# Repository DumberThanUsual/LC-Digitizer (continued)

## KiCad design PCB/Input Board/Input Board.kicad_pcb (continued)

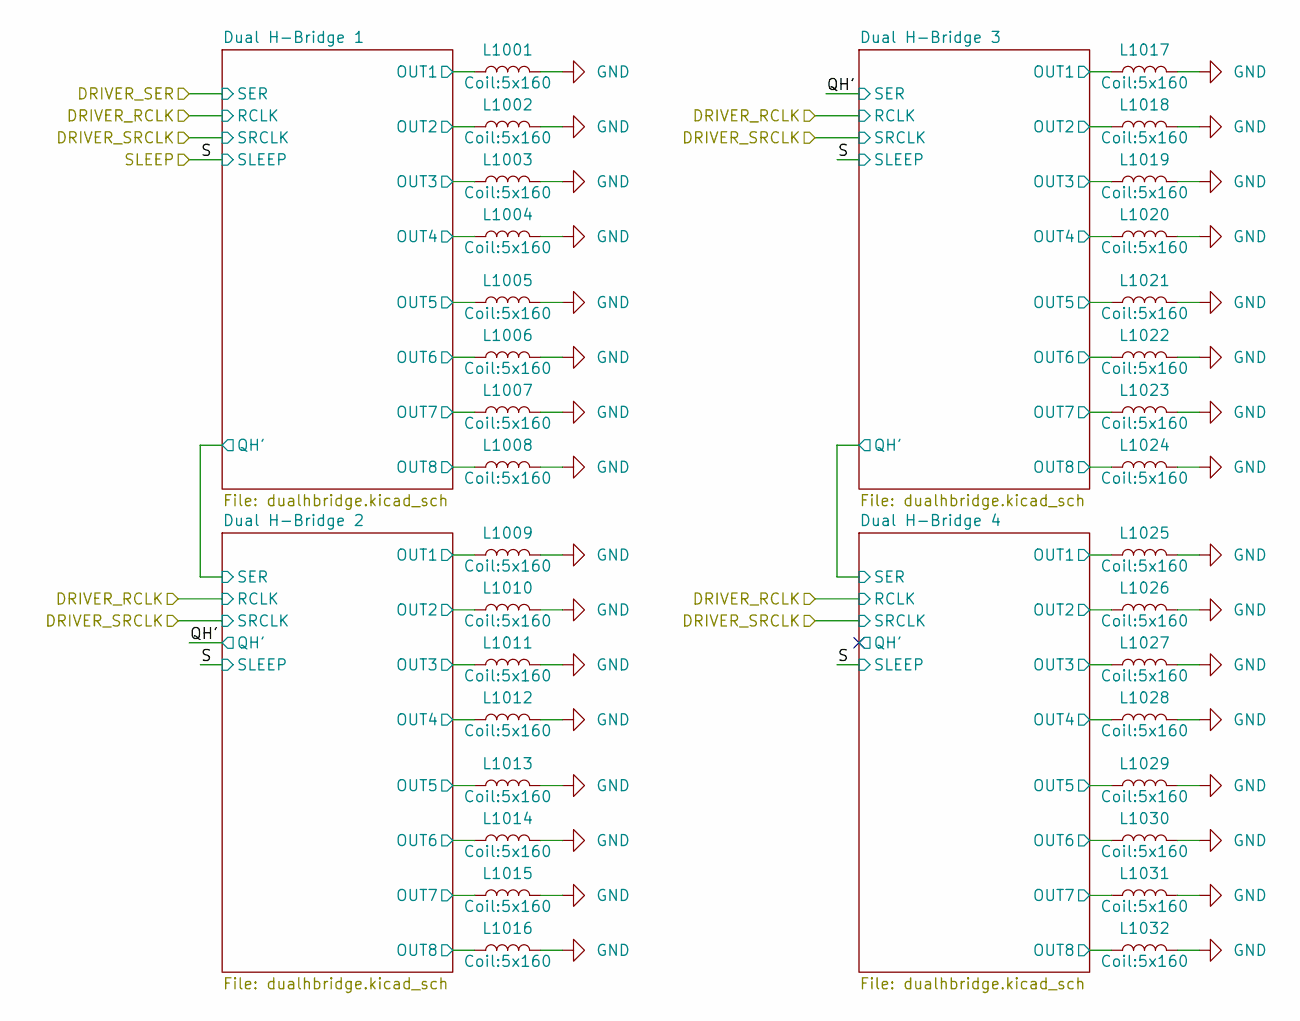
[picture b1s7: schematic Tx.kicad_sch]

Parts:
L1001, L1002, L1003, L1004, L1005, L1006, L1007, L1008, L1009, L1010, L1011, L1012, L1013, L1014, L1015, L1016, L1017, L1018, L1019, L1020, L1021, L1022, L1023, L1024, L1025, L1026, L1027, L1028, L1029, L1030, L1031, L1032: L; 5x160

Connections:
/Transmit Coils/Dual H-Bridge 1/OUT1: L1001.1; also elsewhere on the board
/Transmit Coils/Dual H-Bridge 1/OUT2: L1002.1; also elsewhere on the board
/Transmit Coils/Dual H-Bridge 1/OUT3: L1003.1; also elsewhere on the board
/Transmit Coils/Dual H-Bridge 1/OUT4: L1004.1; also elsewhere on the board
/Transmit Coils/Dual H-Bridge 1/OUT5: L1005.1; also elsewhere on the board
/Transmit Coils/Dual H-Bridge 1/OUT6: L1006.1; also elsewhere on the board
/Transmit Coils/Dual H-Bridge 1/OUT7: L1007.1; also elsewhere on the board
/Transmit Coils/Dual H-Bridge 1/OUT8: L1008.1; also elsewhere on the board
/Transmit Coils/Dual H-Bridge 2/OUT1: L1009.1; also elsewhere on the board
/Transmit Coils/Dual H-Bridge 2/OUT2: L1010.1; also elsewhere on the board
/Transmit Coils/Dual H-Bridge 2/OUT3: L1011.1; also elsewhere on the board
/Transmit Coils/Dual H-Bridge 2/OUT4: L1012.1; also elsewhere on the board
/Transmit Coils/Dual H-Bridge 2/OUT5: L1013.1; also elsewhere on the board
/Transmit Coils/Dual H-Bridge 2/OUT6: L1014.1; also elsewhere on the board
/Transmit Coils/Dual H-Bridge 2/OUT7: L1015.1; also elsewhere on the board
/Transmit Coils/Dual H-Bridge 2/OUT8: L1016.1; also elsewhere on the board
/Transmit Coils/Dual H-Bridge 3/OUT1: L1017.1; also elsewhere on the board
/Transmit Coils/Dual H-Bridge 3/OUT2: L1018.1; also elsewhere on the board
/Transmit Coils/Dual H-Bridge 3/OUT3: L1019.1; also elsewhere on the board
/Transmit Coils/Dual H-Bridge 3/OUT4: L1020.1; also elsewhere on the board
/Transmit Coils/Dual H-Bridge 3/OUT5: L1021.1; also elsewhere on the board
/Transmit Coils/Dual H-Bridge 3/OUT6: L1022.1; also elsewhere on the board
/Transmit Coils/Dual H-Bridge 3/OUT7: L1023.1; also elsewhere on the board
/Transmit Coils/Dual H-Bridge 3/OUT8: L1024.1; also elsewhere on the board
/Transmit Coils/Dual H-Bridge 4/OUT1: L1025.1; also elsewhere on the board
/Transmit Coils/Dual H-Bridge 4/OUT2: L1026.1; also elsewhere on the board
/Transmit Coils/Dual H-Bridge 4/OUT3: L1027.1; also elsewhere on the board
/Transmit Coils/Dual H-Bridge 4/OUT4: L1028.1; also elsewhere on the board
/Transmit Coils/Dual H-Bridge 4/OUT5: L1029.1; also elsewhere on the board
/Transmit Coils/Dual H-Bridge 4/OUT6: L1030.1; also elsewhere on the board
/Transmit Coils/Dual H-Bridge 4/OUT7: L1031.1; also elsewhere on the board
/Transmit Coils/Dual H-Bridge 4/OUT8: L1032.1; also elsewhere on the board
GND: L1001.2, L1002.2, L1003.2, L1004.2, L1005.2, L1006.2, L1007.2, L1008.2, L1009.2, L1010.2, L1011.2, L1012.2, L1013.2, L1014.2, L1015.2, L1016.2, L1017.2, L1018.2, L1019.2, L1020.2, L1021.2, L1022.2, L1023.2, L1024.2, L1025.2, L1026.2, L1027.2, L1028.2, L1029.2, L1030.2, L1031.2, L1032.2; also elsewhere on the board

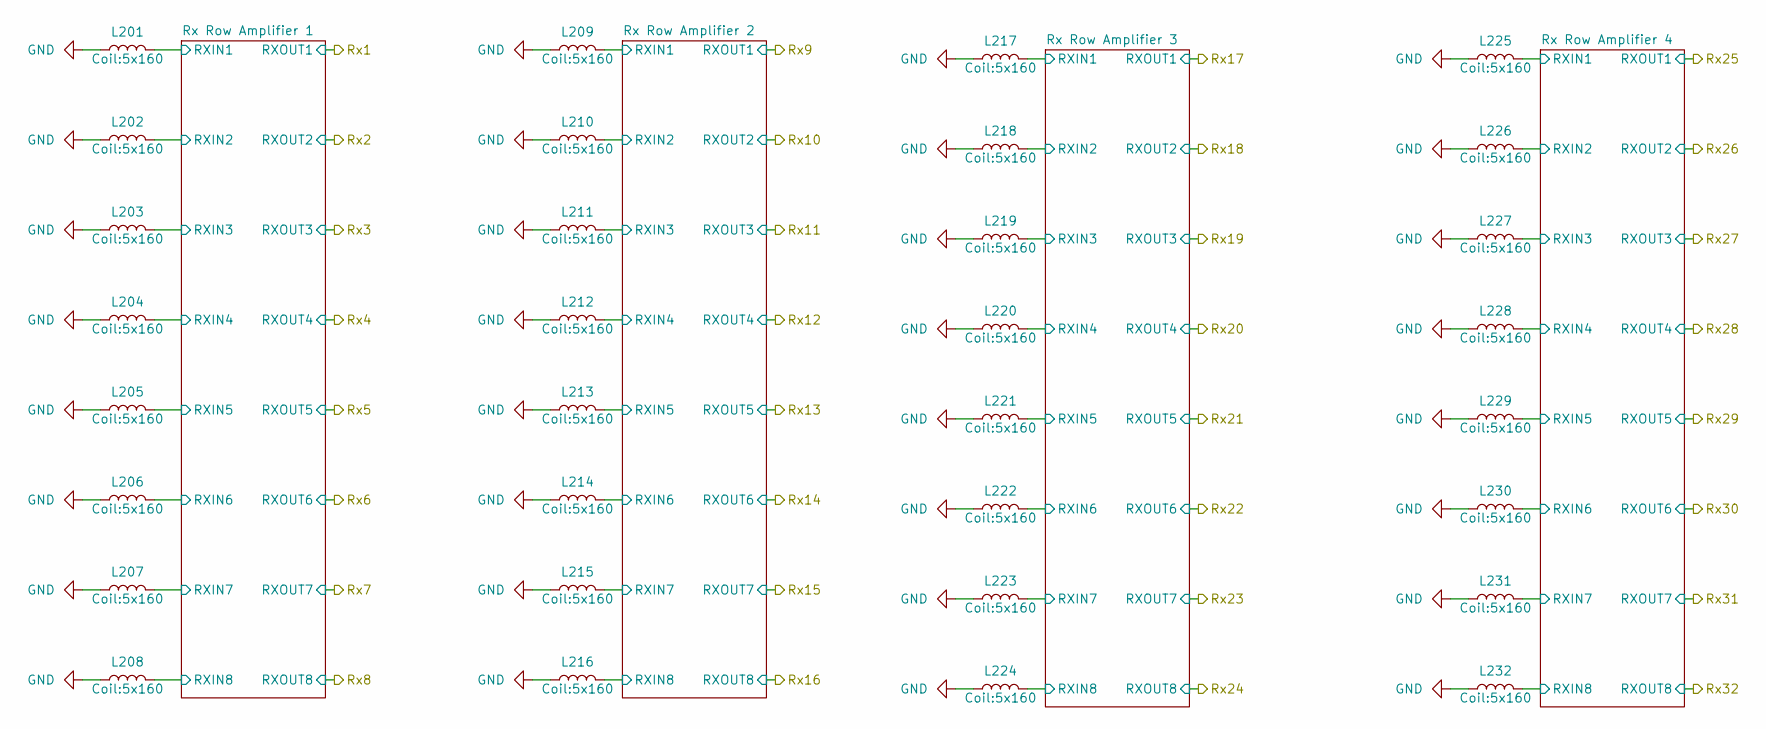
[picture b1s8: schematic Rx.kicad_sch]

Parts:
L201, L202, L203, L204, L205, L206, L207, L208, L209, L210, L211, L212, L213, L214, L215, L216, L217, L218, L219, L220, L221, L222, L223, L224, L225, L226, L227, L228, L229, L230, L231, L232: L; 5x160

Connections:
/Receiver Stage/Rx Row Amplifier 1/RXIN1: L201.2; also elsewhere on the board
/Receiver Stage/Rx Row Amplifier 1/RXIN2: L202.2; also elsewhere on the board
/Receiver Stage/Rx Row Amplifier 1/RXIN3: L203.2; also elsewhere on the board
/Receiver Stage/Rx Row Amplifier 1/RXIN4: L204.2; also elsewhere on the board
/Receiver Stage/Rx Row Amplifier 1/RXIN5: L205.2; also elsewhere on the board
/Receiver Stage/Rx Row Amplifier 1/RXIN6: L206.2; also elsewhere on the board
/Receiver Stage/Rx Row Amplifier 1/RXIN7: L207.2; also elsewhere on the board
/Receiver Stage/Rx Row Amplifier 1/RXIN8: L208.2; also elsewhere on the board
/Receiver Stage/Rx Row Amplifier 2/RXIN1: L209.2; also elsewhere on the board
/Receiver Stage/Rx Row Amplifier 2/RXIN2: L210.2; also elsewhere on the board
/Receiver Stage/Rx Row Amplifier 2/RXIN3: L211.2; also elsewhere on the board
/Receiver Stage/Rx Row Amplifier 2/RXIN4: L212.2; also elsewhere on the board
/Receiver Stage/Rx Row Amplifier 2/RXIN5: L213.2; also elsewhere on the board
/Receiver Stage/Rx Row Amplifier 2/RXIN6: L214.2; also elsewhere on the board
/Receiver Stage/Rx Row Amplifier 2/RXIN7: L215.2; also elsewhere on the board
/Receiver Stage/Rx Row Amplifier 2/RXIN8: L216.2; also elsewhere on the board
/Receiver Stage/Rx Row Amplifier 3/RXIN1: L217.2; also elsewhere on the board
/Receiver Stage/Rx Row Amplifier 3/RXIN2: L218.2; also elsewhere on the board
/Receiver Stage/Rx Row Amplifier 3/RXIN3: L219.2; also elsewhere on the board
/Receiver Stage/Rx Row Amplifier 3/RXIN4: L220.2; also elsewhere on the board
/Receiver Stage/Rx Row Amplifier 3/RXIN5: L221.2; also elsewhere on the board
/Receiver Stage/Rx Row Amplifier 3/RXIN6: L222.2; also elsewhere on the board
/Receiver Stage/Rx Row Amplifier 3/RXIN7: L223.2; also elsewhere on the board
/Receiver Stage/Rx Row Amplifier 3/RXIN8: L224.2; also elsewhere on the board
/Receiver Stage/Rx Row Amplifier 4/RXIN1: L225.2; also elsewhere on the board
/Receiver Stage/Rx Row Amplifier 4/RXIN2: L226.2; also elsewhere on the board
/Receiver Stage/Rx Row Amplifier 4/RXIN3: L227.2; also elsewhere on the board
/Receiver Stage/Rx Row Amplifier 4/RXIN4: L228.2; also elsewhere on the board
/Receiver Stage/Rx Row Amplifier 4/RXIN5: L229.2; also elsewhere on the board
/Receiver Stage/Rx Row Amplifier 4/RXIN6: L230.2; also elsewhere on the board
/Receiver Stage/Rx Row Amplifier 4/RXIN7: L231.2; also elsewhere on the board
/Receiver Stage/Rx Row Amplifier 4/RXIN8: L232.2; also elsewhere on the board
GND: L201.1, L202.1, L203.1, L204.1, L205.1, L206.1, L207.1, L208.1, L209.1, L210.1, L211.1, L212.1, L213.1, L214.1, L215.1, L216.1, L217.1, L218.1, L219.1, L220.1, L221.1, L222.1, L223.1, L224.1, L225.1, L226.1, L227.1, L228.1, L229.1, L230.1, L231.1, L232.1; also elsewhere on the board

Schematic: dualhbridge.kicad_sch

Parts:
C1101, C1102, C1103, C1104, C1105: 100n; C_0603_1608Metric
U1101: 74HCS95; DHVQFN-16-1EP_2.5x3.5mm_P0.5mm_EP1x2mm
U1102, U1103, U1104, U1105: DRV8837; WSON-8-1EP_2x2mm_P0.5mm_EP0.9x1.6mm

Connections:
+5V: C1101.2, C1102.2, C1103.2, C1104.2, C1105.2, U1101.10 (~SRCLR), U1101.16 (VCC), U1102.1 (VM), U1102.8 (VCC), U1103.1 (VM), U1103.8 (VCC), U1104.1 (VM), U1104.8 (VCC), U1105.1 (VM), U1105.8 (VCC); also elsewhere on the board
/Measurement & Control/TX_RCLK: U1101.12 (RCLK); also elsewhere on the board
/Measurement & Control/TX_SDO: U1101.14 (SER); also elsewhere on the board
/Measurement & Control/TX_SLEEP: U1102.7 (~SLEEP), U1103.7 (~SLEEP), U1104.7 (~SLEEP), U1105.7 (~SLEEP); also elsewhere on the board
/Measurement & Control/TX_SRCLK: U1101.11 (SRCLK); also elsewhere on the board
/Transmit Coils/Dual H-Bridge 1/OUT1: U1102.2 (OUT1); also elsewhere on the board
/Transmit Coils/Dual H-Bridge 1/OUT2: U1102.3 (OUT2); also elsewhere on the board
/Transmit Coils/Dual H-Bridge 1/OUT3: U1103.2 (OUT1); also elsewhere on the board
/Transmit Coils/Dual H-Bridge 1/OUT4: U1103.3 (OUT2); also elsewhere on the board
/Transmit Coils/Dual H-Bridge 1/OUT5: U1104.2 (OUT1); also elsewhere on the board
/Transmit Coils/Dual H-Bridge 1/OUT6: U1104.3 (OUT2); also elsewhere on the board
/Transmit Coils/Dual H-Bridge 1/OUT7: U1105.2 (OUT1); also elsewhere on the board
/Transmit Coils/Dual H-Bridge 1/OUT8: U1105.3 (OUT2); also elsewhere on the board
/Transmit Coils/Dual H-Bridge 1/QH': U1101.9 (QH'); also elsewhere on the board
GND: C1101.1, C1102.1, C1103.1, C1104.1, C1105.1, U1101.8 (GND), U1101.13 (~OE), U1101.17, U1102.4 (GND), U1102.9 (GND), U1103.4 (GND), U1103.9 (GND), U1104.4 (GND), U1104.9 (GND), U1105.4 (GND), U1105.9 (GND); also elsewhere on the board
unnamed: U1101.15 (QA), U1102.6 (IN1)
unnamed: U1101.1 (QB), U1102.5 (IN2)
unnamed: U1101.2 (QC), U1103.6 (IN1)
unnamed: U1101.3 (QD), U1103.5 (IN2)
unnamed: U1101.4 (QE), U1104.6 (IN1)
unnamed: U1101.5 (QF), U1104.5 (IN2)
unnamed: U1101.6 (QG), U1105.6 (IN1)
unnamed: U1101.7 (QH), U1105.5 (IN2)

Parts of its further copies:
C1201, C1202, C1203, C1204, C1205, C1301, C1302, C1303, C1304, C1305, C1401, C1402, C1403, C1404, C1405: 100n; C_0603_1608Metric
U1201, U1301, U1401: 74HCS95; DHVQFN-16-1EP_2.5x3.5mm_P0.5mm_EP1x2mm
U1202, U1203, U1204, U1205, U1302, U1303, U1304, U1305, U1402, U1403, U1404, U1405: DRV8837; WSON-8-1EP_2x2mm_P0.5mm_EP0.9x1.6mm

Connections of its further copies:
+5V: C1201.2, C1202.2, C1203.2, C1204.2, C1205.2, C1301.2, C1302.2, C1303.2, C1304.2, C1305.2, C1401.2, C1402.2, C1403.2, C1404.2, C1405.2, U1201.10 (~SRCLR), U1201.16 (VCC), U1202.1 (VM), U1202.8 (VCC), U1203.1 (VM), U1203.8 (VCC), U1204.1 (VM), U1204.8 (VCC), U1205.1 (VM), U1205.8 (VCC), U1301.10 (~SRCLR), U1301.16 (VCC), U1302.1 (VM), U1302.8 (VCC), U1303.1 (VM), U1303.8 (VCC), U1304.1 (VM), U1304.8 (VCC), U1305.1 (VM), U1305.8 (VCC), U1401.10 (~SRCLR), U1401.16 (VCC), U1402.1 (VM), U1402.8 (VCC), U1403.1 (VM), U1403.8 (VCC), U1404.1 (VM), U1404.8 (VCC), U1405.1 (VM), U1405.8 (VCC); also elsewhere on the board
/Measurement & Control/TX_RCLK: U1201.12 (RCLK), U1301.12 (RCLK), U1401.12 (RCLK); also elsewhere on the board
/Measurement & Control/TX_SLEEP: U1202.7 (~SLEEP), U1203.7 (~SLEEP), U1204.7 (~SLEEP), U1205.7 (~SLEEP), U1302.7 (~SLEEP), U1303.7 (~SLEEP), U1304.7 (~SLEEP), U1305.7 (~SLEEP), U1402.7 (~SLEEP), U1403.7 (~SLEEP), U1404.7 (~SLEEP), U1405.7 (~SLEEP); also elsewhere on the board
/Measurement & Control/TX_SRCLK: U1201.11 (SRCLK), U1301.11 (SRCLK), U1401.11 (SRCLK); also elsewhere on the board
/Transmit Coils/Dual H-Bridge 1/QH': U1201.14 (SER); also elsewhere on the board
/Transmit Coils/Dual H-Bridge 2/OUT1: U1202.2 (OUT1); also elsewhere on the board
/Transmit Coils/Dual H-Bridge 2/OUT2: U1202.3 (OUT2); also elsewhere on the board
/Transmit Coils/Dual H-Bridge 2/OUT3: U1203.2 (OUT1); also elsewhere on the board
/Transmit Coils/Dual H-Bridge 2/OUT4: U1203.3 (OUT2); also elsewhere on the board
/Transmit Coils/Dual H-Bridge 2/OUT5: U1204.2 (OUT1); also elsewhere on the board
/Transmit Coils/Dual H-Bridge 2/OUT6: U1204.3 (OUT2); also elsewhere on the board
/Transmit Coils/Dual H-Bridge 2/OUT7: U1205.2 (OUT1); also elsewhere on the board
/Transmit Coils/Dual H-Bridge 2/OUT8: U1205.3 (OUT2); also elsewhere on the board
/Transmit Coils/Dual H-Bridge 3/OUT1: U1302.2 (OUT1); also elsewhere on the board
/Transmit Coils/Dual H-Bridge 3/OUT2: U1302.3 (OUT2); also elsewhere on the board
/Transmit Coils/Dual H-Bridge 3/OUT3: U1303.2 (OUT1); also elsewhere on the board
/Transmit Coils/Dual H-Bridge 3/OUT4: U1303.3 (OUT2); also elsewhere on the board
/Transmit Coils/Dual H-Bridge 3/OUT5: U1304.2 (OUT1); also elsewhere on the board
/Transmit Coils/Dual H-Bridge 3/OUT6: U1304.3 (OUT2); also elsewhere on the board
/Transmit Coils/Dual H-Bridge 3/OUT7: U1305.2 (OUT1); also elsewhere on the board
/Transmit Coils/Dual H-Bridge 3/OUT8: U1305.3 (OUT2); also elsewhere on the board
/Transmit Coils/Dual H-Bridge 3/QH': U1301.9 (QH'), U1401.14 (SER)
/Transmit Coils/Dual H-Bridge 4/OUT1: U1402.2 (OUT1); also elsewhere on the board
/Transmit Coils/Dual H-Bridge 4/OUT2: U1402.3 (OUT2); also elsewhere on the board
/Transmit Coils/Dual H-Bridge 4/OUT3: U1403.2 (OUT1); also elsewhere on the board
/Transmit Coils/Dual H-Bridge 4/OUT4: U1403.3 (OUT2); also elsewhere on the board
/Transmit Coils/Dual H-Bridge 4/OUT5: U1404.2 (OUT1); also elsewhere on the board
/Transmit Coils/Dual H-Bridge 4/OUT6: U1404.3 (OUT2); also elsewhere on the board
/Transmit Coils/Dual H-Bridge 4/OUT7: U1405.2 (OUT1); also elsewhere on the board
/Transmit Coils/Dual H-Bridge 4/OUT8: U1405.3 (OUT2); also elsewhere on the board
/Transmit Coils/Dual H-Bridge 4/QH&apos;: U1401.9 (QH')
/Transmit Coils/QH': U1201.9 (QH'), U1301.14 (SER)
GND: C1201.1, C1202.1, C1203.1, C1204.1, C1205.1, C1301.1, C1302.1, C1303.1, C1304.1, C1305.1, C1401.1, C1402.1, C1403.1, C1404.1, C1405.1, U1201.8 (GND), U1201.13 (~OE), U1201.17, U1202.4 (GND), U1202.9 (GND), U1203.4 (GND), U1203.9 (GND), U1204.4 (GND), U1204.9 (GND), U1205.4 (GND), U1205.9 (GND), U1301.8 (GND), U1301.13 (~OE), U1301.17, U1302.4 (GND), U1302.9 (GND), U1303.4 (GND), U1303.9 (GND), U1304.4 (GND), U1304.9 (GND), U1305.4 (GND), U1305.9 (GND), U1401.8 (GND), U1401.13 (~OE), U1401.17, U1402.4 (GND), U1402.9 (GND), U1403.4 (GND), U1403.9 (GND), U1404.4 (GND), U1404.9 (GND), U1405.4 (GND), U1405.9 (GND); also elsewhere on the board
unnamed: U1201.15 (QA), U1202.6 (IN1)
unnamed: U1201.1 (QB), U1202.5 (IN2)
unnamed: U1201.2 (QC), U1203.6 (IN1)
unnamed: U1201.3 (QD), U1203.5 (IN2)
unnamed: U1201.4 (QE), U1204.6 (IN1)
unnamed: U1201.5 (QF), U1204.5 (IN2)
unnamed: U1201.6 (QG), U1205.6 (IN1)
unnamed: U1201.7 (QH), U1205.5 (IN2)
unnamed: U1301.15 (QA), U1302.6 (IN1)
unnamed: U1301.1 (QB), U1302.5 (IN2)
unnamed: U1301.2 (QC), U1303.6 (IN1)
unnamed: U1301.3 (QD), U1303.5 (IN2)
unnamed: U1301.4 (QE), U1304.6 (IN1)
unnamed: U1301.5 (QF), U1304.5 (IN2)
unnamed: U1301.6 (QG), U1305.6 (IN1)
unnamed: U1301.7 (QH), U1305.5 (IN2)
unnamed: U1401.15 (QA), U1402.6 (IN1)
unnamed: U1401.1 (QB), U1402.5 (IN2)
unnamed: U1401.2 (QC), U1403.6 (IN1)
unnamed: U1401.3 (QD), U1403.5 (IN2)
unnamed: U1401.4 (QE), U1404.6 (IN1)
unnamed: U1401.5 (QF), U1404.5 (IN2)
unnamed: U1401.6 (QG), U1405.6 (IN1)
unnamed: U1401.7 (QH), U1405.5 (IN2)

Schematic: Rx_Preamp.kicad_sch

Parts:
C301, C302, C303, C304, C306, C307, C309, C310, C311, C312, C313, C314, C315, C316, C317, C318: 1.8n; C_0603_1608Metric
C305, C308: 100n; C_0603_1608Metric
R301, R302, R303, R304, R307, R308, R309, R310, R313, R314, R315, R316, R319, R320, R321, R322: 1k; R_0603_1608Metric
R305, R306, R311, R312, R317, R318, R323, R324: 15k; R_0603_1608Metric
U301, U302: TSV994; SOIC-14_3.9x8.7mm_P1.27mm

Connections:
1.65V: C303.2, C304.2, C309.2, C310.2, C313.2, C314.2, C317.2, C318.2, R301.1, R302.1, R307.1, R308.1, R313.1, R314.1, R319.1, R320.1; also elsewhere on the board
+3.3VA: C305.1, C308.1, U301.4 (V+), U302.4 (V+); also elsewhere on the board
/Mux & Amplifier 1/In1: R305.2, U301.1; also elsewhere on the board
/Mux & Amplifier 1/In2: R306.2, U301.7; also elsewhere on the board
/Mux & Amplifier 1/In3: R311.2, U301.8; also elsewhere on the board
/Mux & Amplifier 1/In4: R312.2, U301.14; also elsewhere on the board
/Mux & Amplifier 1/In5: R317.2, U302.1; also elsewhere on the board
/Mux & Amplifier 1/In6: R318.2, U302.7; also elsewhere on the board
/Mux & Amplifier 1/In7: R323.2, U302.8; also elsewhere on the board
/Mux & Amplifier 1/In8: R324.2, U302.14; also elsewhere on the board
/Receiver Stage/Rx Row Amplifier 1/RXIN1: C301.2; also elsewhere on the board
/Receiver Stage/Rx Row Amplifier 1/RXIN2: C302.2; also elsewhere on the board
/Receiver Stage/Rx Row Amplifier 1/RXIN3: C306.2; also elsewhere on the board
/Receiver Stage/Rx Row Amplifier 1/RXIN4: C307.2; also elsewhere on the board
/Receiver Stage/Rx Row Amplifier 1/RXIN5: C311.2; also elsewhere on the board
/Receiver Stage/Rx Row Amplifier 1/RXIN6: C312.2; also elsewhere on the board
/Receiver Stage/Rx Row Amplifier 1/RXIN7: C315.2; also elsewhere on the board
/Receiver Stage/Rx Row Amplifier 1/RXIN8: C316.2; also elsewhere on the board
GND: C305.2, C308.2, U301.11 (V-), U302.11 (V-); also elsewhere on the board
unnamed: C303.1, R303.2
unnamed: C304.1, R304.2
unnamed: C309.1, R309.2
unnamed: C310.1, R310.2
unnamed: C313.1, R315.2
unnamed: C314.1, R316.2
unnamed: C317.1, R321.2
unnamed: C318.1, R322.2
unnamed: C301.1, R301.2, U301.3 (+)
unnamed: R303.1, R305.1, U301.2 (-)
unnamed: C302.1, R302.2, U301.5 (+)
unnamed: R304.1, R306.1, U301.6 (-)
unnamed: C306.1, R307.2, U301.10 (+)
unnamed: R309.1, R311.1, U301.9 (-)
unnamed: C307.1, R308.2, U301.12 (+)
unnamed: R310.1, R312.1, U301.13 (-)
unnamed: C311.1, R313.2, U302.3 (+)
unnamed: R315.1, R317.1, U302.2 (-)
unnamed: C312.1, R314.2, U302.5 (+)
unnamed: R316.1, R318.1, U302.6 (-)
unnamed: C315.1, R319.2, U302.10 (+)
unnamed: R321.1, R323.1, U302.9 (-)
unnamed: C316.1, R320.2, U302.12 (+)
unnamed: R322.1, R324.1, U302.13 (-)

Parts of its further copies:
C401, C402, C403, C404, C406, C407, C409, C410, C411, C412, C413, C414, C415, C416, C417, C418, C501, C502, C503, C504, C506, C507, C509, C510, C511, C512, C513, C514, C515, C516, C517, C518, C601, C602, C603, C604, C606, C607, C609, C610, C611, C612, C613, C614, C615, C616, C617, C618: 1.8n; C_0603_1608Metric
C405, C408, C505, C508, C605, C608: 100n; C_0603_1608Metric
R401, R402, R403, R404, R407, R408, R409, R410, R413, R414, R415, R416, R419, R420, R421, R422, R501, R502, R503, R504, R507, R508, R509, R510, R513, R514, R515, R516, R519, R520, R521, R522, R601, R602, R603, R604, R607, R608, R609, R610, R613, R614, R615, R616, R619, R620, R621, R622: 1k; R_0603_1608Metric
R405, R406, R411, R412, R417, R418, R423, R424, R505, R506, R511, R512, R517, R518, R523, R524, R605, R606, R611, R612, R617, R618, R623, R624: 15k; R_0603_1608Metric
U401, U402, U501, U502, U601, U602: TSV994; SOIC-14_3.9x8.7mm_P1.27mm

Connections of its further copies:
1.65V: C403.2, C404.2, C409.2, C410.2, C413.2, C414.2, C417.2, C418.2, C503.2, C504.2, C509.2, C510.2, C513.2, C514.2, C517.2, C518.2, C603.2, C604.2, C609.2, C610.2, C613.2, C614.2, C617.2, C618.2, R401.1, R402.1, R407.1, R408.1, R413.1, R414.1, R419.1, R420.1, R501.1, R502.1, R507.1, R508.1, R513.1, R514.1, R519.1, R520.1, R601.1, R602.1, R607.1, R608.1, R613.1, R614.1, R619.1, R620.1; also elsewhere on the board
+3.3VA: C405.1, C408.1, C505.1, C508.1, C605.1, C608.1, U401.4 (V+), U402.4 (V+), U501.4 (V+), U502.4 (V+), U601.4 (V+), U602.4 (V+); also elsewhere on the board
/Mux & Amplifier 1/In9: R405.2, U401.1; also elsewhere on the board
/Mux & Amplifier 1/In10: R406.2, U401.7; also elsewhere on the board
/Mux & Amplifier 1/In11: R411.2, U401.8; also elsewhere on the board
/Mux & Amplifier 1/In12: R412.2, U401.14; also elsewhere on the board
/Mux & Amplifier 1/In13: R417.2, U402.1; also elsewhere on the board
/Mux & Amplifier 1/In14: R418.2, U402.7; also elsewhere on the board
/Mux & Amplifier 1/In15: R423.2, U402.8; also elsewhere on the board
/Mux & Amplifier 1/In16: R424.2, U402.14; also elsewhere on the board
/Mux & Amplifier 2/In1: R505.2, U501.1; also elsewhere on the board
/Mux & Amplifier 2/In2: R506.2, U501.7; also elsewhere on the board
/Mux & Amplifier 2/In3: R511.2, U501.8; also elsewhere on the board
/Mux & Amplifier 2/In4: R512.2, U501.14; also elsewhere on the board
/Mux & Amplifier 2/In5: R517.2, U502.1; also elsewhere on the board
/Mux & Amplifier 2/In6: R518.2, U502.7; also elsewhere on the board
/Mux & Amplifier 2/In7: R523.2, U502.8; also elsewhere on the board
/Mux & Amplifier 2/In8: R524.2, U502.14; also elsewhere on the board
/Mux & Amplifier 2/In9: R605.2, U601.1; also elsewhere on the board
/Mux & Amplifier 2/In10: R606.2, U601.7; also elsewhere on the board
/Mux & Amplifier 2/In11: R611.2, U601.8; also elsewhere on the board
/Mux & Amplifier 2/In12: R612.2, U601.14; also elsewhere on the board
/Mux & Amplifier 2/In13: R617.2, U602.1; also elsewhere on the board
/Mux & Amplifier 2/In14: R618.2, U602.7; also elsewhere on the board
/Mux & Amplifier 2/In15: R623.2, U602.8; also elsewhere on the board
/Mux & Amplifier 2/In16: R624.2, U602.14; also elsewhere on the board
/Receiver Stage/Rx Row Amplifier 2/RXIN1: C401.2; also elsewhere on the board
/Receiver Stage/Rx Row Amplifier 2/RXIN2: C402.2; also elsewhere on the board
/Receiver Stage/Rx Row Amplifier 2/RXIN3: C406.2; also elsewhere on the board
/Receiver Stage/Rx Row Amplifier 2/RXIN4: C407.2; also elsewhere on the board
/Receiver Stage/Rx Row Amplifier 2/RXIN5: C411.2; also elsewhere on the board
/Receiver Stage/Rx Row Amplifier 2/RXIN6: C412.2; also elsewhere on the board
/Receiver Stage/Rx Row Amplifier 2/RXIN7: C415.2; also elsewhere on the board
/Receiver Stage/Rx Row Amplifier 2/RXIN8: C416.2; also elsewhere on the board
/Receiver Stage/Rx Row Amplifier 3/RXIN1: C501.2; also elsewhere on the board
/Receiver Stage/Rx Row Amplifier 3/RXIN2: C502.2; also elsewhere on the board
/Receiver Stage/Rx Row Amplifier 3/RXIN3: C506.2; also elsewhere on the board
/Receiver Stage/Rx Row Amplifier 3/RXIN4: C507.2; also elsewhere on the board
/Receiver Stage/Rx Row Amplifier 3/RXIN5: C511.2; also elsewhere on the board
/Receiver Stage/Rx Row Amplifier 3/RXIN6: C512.2; also elsewhere on the board
/Receiver Stage/Rx Row Amplifier 3/RXIN7: C515.2; also elsewhere on the board
/Receiver Stage/Rx Row Amplifier 3/RXIN8: C516.2; also elsewhere on the board
/Receiver Stage/Rx Row Amplifier 4/RXIN1: C601.2; also elsewhere on the board
/Receiver Stage/Rx Row Amplifier 4/RXIN2: C602.2; also elsewhere on the board
/Receiver Stage/Rx Row Amplifier 4/RXIN3: C606.2; also elsewhere on the board
/Receiver Stage/Rx Row Amplifier 4/RXIN4: C607.2; also elsewhere on the board
/Receiver Stage/Rx Row Amplifier 4/RXIN5: C611.2; also elsewhere on the board
/Receiver Stage/Rx Row Amplifier 4/RXIN6: C612.2; also elsewhere on the board
/Receiver Stage/Rx Row Amplifier 4/RXIN7: C615.2; also elsewhere on the board
/Receiver Stage/Rx Row Amplifier 4/RXIN8: C616.2; also elsewhere on the board
GND: C405.2, C408.2, C505.2, C508.2, C605.2, C608.2, U401.11 (V-), U402.11 (V-), U501.11 (V-), U502.11 (V-), U601.11 (V-), U602.11 (V-); also elsewhere on the board
unnamed: C403.1, R403.2
unnamed: C404.1, R404.2
unnamed: C409.1, R409.2
unnamed: C410.1, R410.2
unnamed: C413.1, R415.2
unnamed: C414.1, R416.2
unnamed: C417.1, R421.2
unnamed: C418.1, R422.2
unnamed: C503.1, R503.2
unnamed: C504.1, R504.2
unnamed: C509.1, R509.2
unnamed: C510.1, R510.2
unnamed: C513.1, R515.2
unnamed: C514.1, R516.2
unnamed: C517.1, R521.2
unnamed: C518.1, R522.2
unnamed: C603.1, R603.2
unnamed: C604.1, R604.2
unnamed: C609.1, R609.2
unnamed: C610.1, R610.2
unnamed: C613.1, R615.2
unnamed: C614.1, R616.2
unnamed: C617.1, R621.2
unnamed: C618.1, R622.2
unnamed: C401.1, R401.2, U401.3 (+)
unnamed: R403.1, R405.1, U401.2 (-)
unnamed: C402.1, R402.2, U401.5 (+)
unnamed: R404.1, R406.1, U401.6 (-)
unnamed: C406.1, R407.2, U401.10 (+)
unnamed: R409.1, R411.1, U401.9 (-)
unnamed: C407.1, R408.2, U401.12 (+)
unnamed: R410.1, R412.1, U401.13 (-)
unnamed: C411.1, R413.2, U402.3 (+)
unnamed: R415.1, R417.1, U402.2 (-)
unnamed: C412.1, R414.2, U402.5 (+)
unnamed: R416.1, R418.1, U402.6 (-)
unnamed: C415.1, R419.2, U402.10 (+)
unnamed: R421.1, R423.1, U402.9 (-)
unnamed: C416.1, R420.2, U402.12 (+)
unnamed: R422.1, R424.1, U402.13 (-)
unnamed: C501.1, R501.2, U501.3 (+)
unnamed: R503.1, R505.1, U501.2 (-)
unnamed: C502.1, R502.2, U501.5 (+)
unnamed: R504.1, R506.1, U501.6 (-)
unnamed: C506.1, R507.2, U501.10 (+)
unnamed: R509.1, R511.1, U501.9 (-)
unnamed: C507.1, R508.2, U501.12 (+)
unnamed: R510.1, R512.1, U501.13 (-)
unnamed: C511.1, R513.2, U502.3 (+)
unnamed: R515.1, R517.1, U502.2 (-)
unnamed: C512.1, R514.2, U502.5 (+)
unnamed: R516.1, R518.1, U502.6 (-)
unnamed: C515.1, R519.2, U502.10 (+)
unnamed: R521.1, R523.1, U502.9 (-)
unnamed: C516.1, R520.2, U502.12 (+)
unnamed: R522.1, R524.1, U502.13 (-)
unnamed: C601.1, R601.2, U601.3 (+)
unnamed: R603.1, R605.1, U601.2 (-)
unnamed: C602.1, R602.2, U601.5 (+)
unnamed: R604.1, R606.1, U601.6 (-)
unnamed: C606.1, R607.2, U601.10 (+)
unnamed: R609.1, R611.1, U601.9 (-)
unnamed: C607.1, R608.2, U601.12 (+)
unnamed: R610.1, R612.1, U601.13 (-)
unnamed: C611.1, R613.2, U602.3 (+)
unnamed: R615.1, R617.1, U602.2 (-)
unnamed: C612.1, R614.2, U602.5 (+)
unnamed: R616.1, R618.1, U602.6 (-)
unnamed: C615.1, R619.2, U602.10 (+)
unnamed: R621.1, R623.1, U602.9 (-)
unnamed: C616.1, R620.2, U602.12 (+)
unnamed: R622.1, R624.1, U602.13 (-)

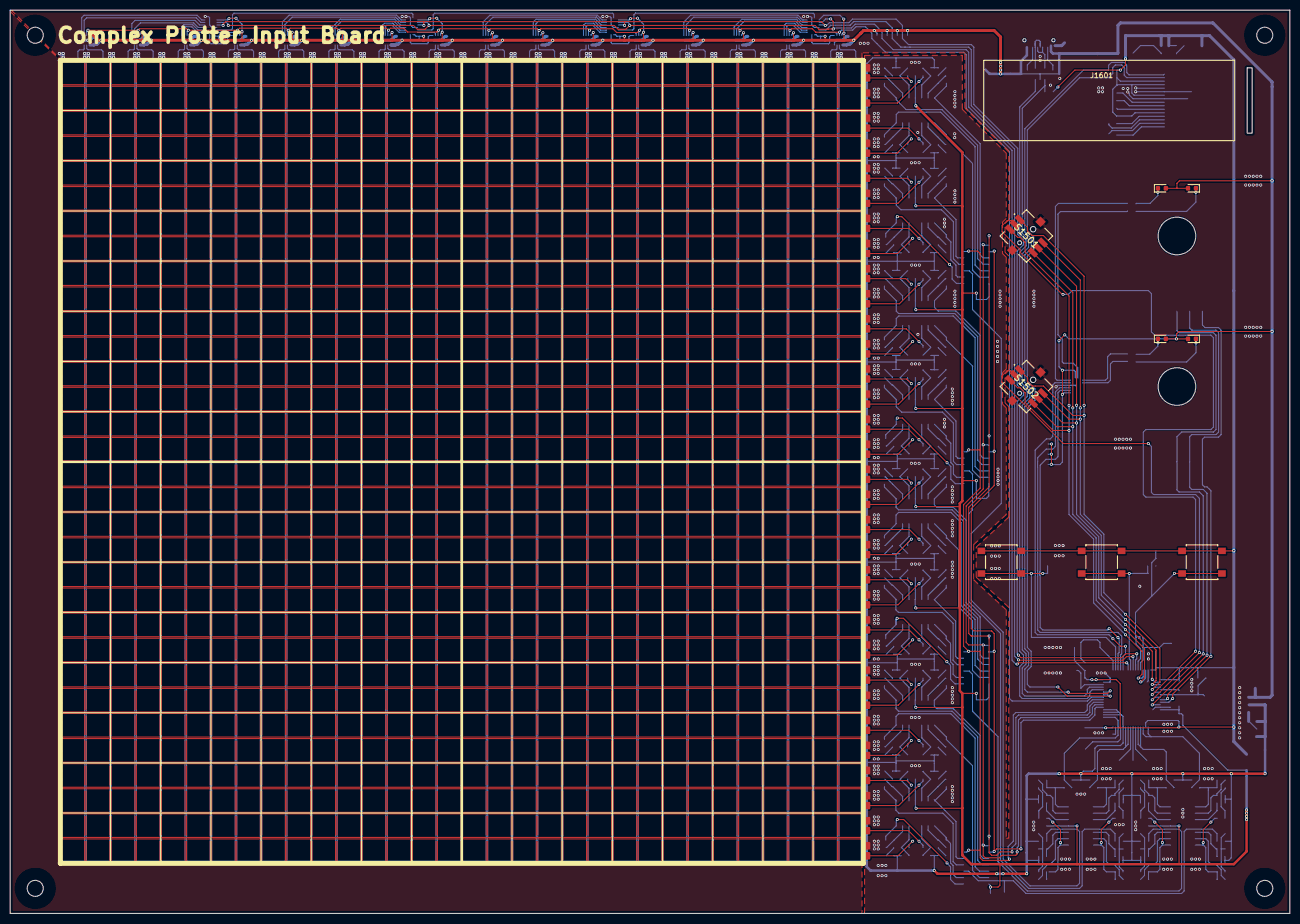
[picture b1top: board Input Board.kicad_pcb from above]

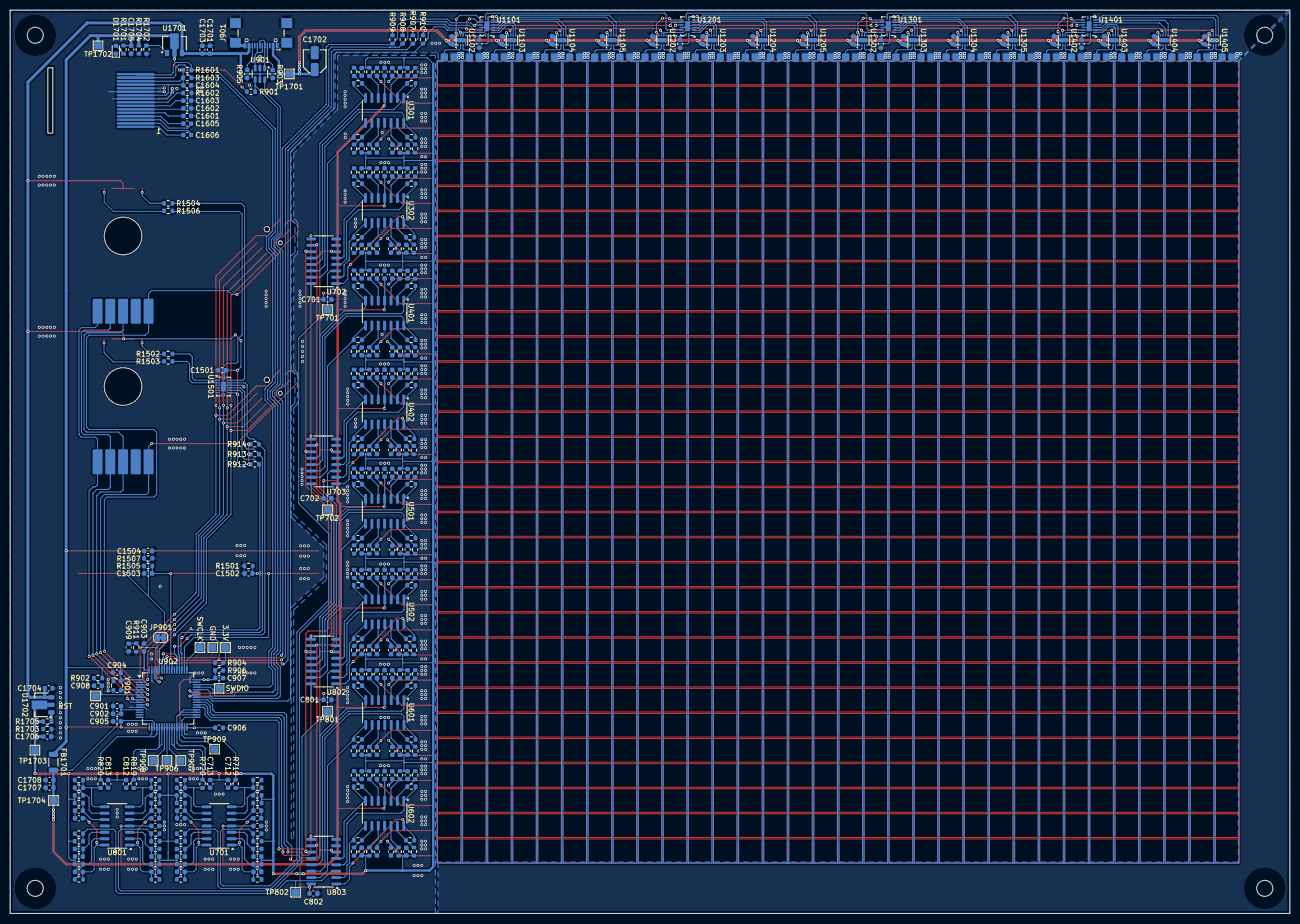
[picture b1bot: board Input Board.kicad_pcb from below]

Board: 2 copper layers, 255.0 x 180.0 mm, 451 parts (403 on the bottom side), 331 nets.

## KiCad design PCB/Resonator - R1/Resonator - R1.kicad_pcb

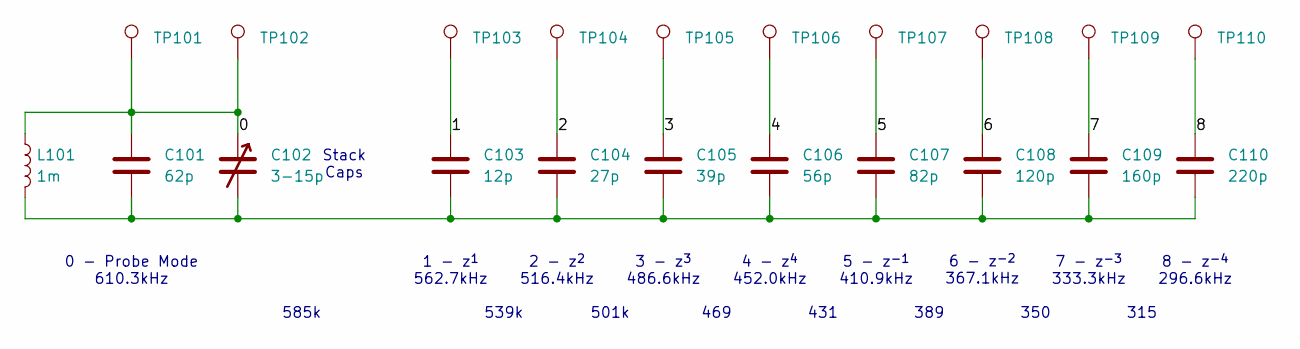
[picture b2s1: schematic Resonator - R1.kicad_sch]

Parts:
C101: 62p; C_0603_1608Metric
C102: 3-15p
C103: 12p; C_0603_1608Metric
C104: 27p; C_0603_1608Metric
C105: 39p; C_0603_1608Metric
C106: 56p; C_0603_1608Metric
C107: 82p; C_0603_1608Metric
C108: 120p; C_0603_1608Metric
C109: 160p; C_0603_1608Metric
C110: 220p; C_0603_1608Metric
L101: 1m; L
TP101, TP102: TestPoint; 5mm 112.5
TP103, TP104, TP105, TP106, TP107, TP108, TP109, TP110: TestPoint; 7mm 20

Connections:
/0: C101.1, C102.1, L101.1, TP101.1, TP102.1
/1: C103.1, TP103.1
/2: C104.1, TP104.1
/3: C105.1, TP105.1
/4: C106.1, TP106.1
/5: C107.1, TP107.1
/6: C108.1, TP108.1
/7: C109.1, TP109.1
/8: C110.1, TP110.1
unnamed: C101.2, C102.2, C103.2, C104.2, C105.2, C106.2, C107.2, C108.2, C109.2, C110.2, L101.2

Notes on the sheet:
8 - z^{-4} 296.6kHz
0 - Probe Mode 610.3kHz
469
Stack Caps
3 - z^{3} 486.6kHz
389
2 - z^{2} 516.4kHz
1 - z^{1} 562.7kHz
4 - z^{4} 452.0kHz
431
5 - z^{-1} 410.9kHz
7 - z^{-3} 333.3kHz
350
315
501k
6 - z^{-2} 367.1kHz
539k
585k

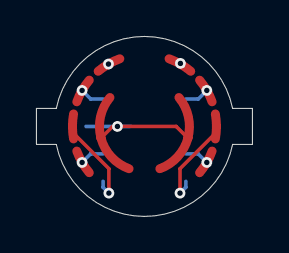
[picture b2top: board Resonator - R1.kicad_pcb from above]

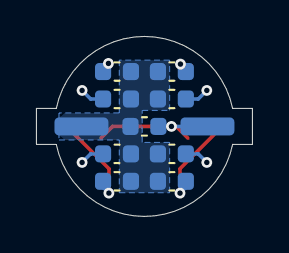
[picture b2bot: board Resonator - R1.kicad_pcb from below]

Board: 2 copper layers, 12.0 x 10.0 mm, 20 parts (10 on the bottom side), 10 nets.

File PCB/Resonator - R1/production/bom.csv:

Designator,Footprint,Quantity,Value,LCSC Part #
C101,0603,1,62p,
C103,0603,1,12p,
C104,0603,1,27p,
C105,0603,1,39p,
C106,0603,1,56p,
C107,0603,1,82p,
C108,0603,1,120p,
C109,0603,1,160p,
C110,0603,1,220p,
L101,L,1,1m,
"TP101, TP102",5mm 112.5,2,TestPoint,
"TP103, TP104, TP105, TP106, TP107, TP108, TP109, TP110",7mm 20,8,TestPoint,

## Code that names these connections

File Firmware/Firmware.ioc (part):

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Mcu.Name=STM32F303R(B-C)Tx
Mcu.Package=LQFP64
Mcu.UserName=STM32F303RBTx
PA10.GPIOParameters=GPIO_Label
PA10.GPIO_Label=OLED_SDA
PA10.Mode=I2C
PA10.Signal=I2C2_SDA
PA11.Mode=Device
PA11.Signal=USB_DM
PA12.Mode=Device
PA12.Signal=USB_DP
PA13.Mode=Serial_Wire
PA13.Signal=SYS_JTMS-SWDIO
PA14.Mode=Serial_Wire
PA14.Signal=SYS_JTCK-SWCLK
PA15.GPIOParameters=GPIO_Label
PA15.GPIO_Label=PUSH_1
PA15.Signal=GPIO_Input
PA4.GPIOParameters=GPIO_Label
PA4.GPIO_Label=RX1_COMP
PA4.Mode=INM
PA4.Signal=COMP3_INM
PA5.GPIOParameters=GPIO_Label
PA5.GPIO_Label=RX3_COMP
PA5.Mode=INM
PA5.Signal=COMP5_INM
PA6.GPIOParameters=GPIO_Label
PA6.GPIO_Label=RX3_ADC
PA6.Mode=IN3-Single-Ended
PA6.Signal=ADC2_IN3
PA7.GPIOParameters=GPIO_Label
PA7.GPIO_Label=TP908
PA7.Signal=GPIO_Output
PA8.GPIOParameters=GPIO_Label
PA8.GPIO_Label=TX_SLEEP
PA8.Signal=GPIO_Output
PA9.GPIOParameters=GPIO_Label
PA9.GPIO_Label=OLED_SCL
PA9.Mode=I2C
PA9.Signal=I2C2_SCL
PB0.GPIOParameters=GPIO_Label
PB0.GPIO_Label=RX2_COMP
PB0.Mode=INP
PB0.Signal=COMP4_INP
PB1.GPIOParameters=GPIO_Label
PB1.GPIO_Label=RX2_ADC
PB1.Mode=IN1-Single-Ended
PB1.Signal=ADC3_IN1
PB10.GPIOParameters=GPIO_Label
PB10.GPIO_Label=TP909
PB10.Signal=GPIO_Output
PB11.GPIOParameters=GPIO_Label
PB11.GPIO_Label=RX4_COMP
PB11.Mode=INP
PB11.Signal=COMP6_INP
PB12.GPIOParameters=GPIO_Label
PB12.GPIO_Label=RX4_ADC
PB12.Mode=IN3-Single-Ended
PB12.Signal=ADC4_IN3
PB13.GPIOParameters=GPIO_Label
PB13.GPIO_Label=VREF
PB13.Mode=INP
PB13.Signal=COMP5_INP
PB14.GPIOParameters=GPIO_Label
PB14.GPIO_Label=VREF
PB14.Mode=INP
PB14.Signal=COMP3_INP
PB15.GPIOParameters=GPIO_Label
PB15.GPIO_Label=VREF
PB15.Mode=INM
PB15.Signal=COMP6_INM
PB2.GPIOParameters=GPIO_Label
PB2.GPIO_Label=VREF
PB2.Mode=INM
PB2.Signal=COMP4_INM
PB3.GPIOParameters=GPIO_Label
PB3.GPIO_Label=TX_CLK
PB3.Mode=TX_Only_Simplex_Unidirect_Master
PB3.Signal=SPI1_SCK
PB4.GPIOParameters=GPIO_Label
PB4.GPIO_Label=PUSH_2
PB4.Signal=GPIO_Output
PB5.GPIOParameters=GPIO_Label
PB5.GPIO_Label=TX_MOSI
PB5.Mode=TX_Only_Simplex_Unidirect_Master
PB5.Signal=SPI1_MOSI
PB6.GPIOParameters=GPIO_Label
PB6.GPIO_Label=TX_RCLK
PB6.Signal=GPIO_Output
PB7.GPIOParameters=GPIO_Label
PB7.GPIO_Label=PUSH_3
PB7.Signal=GPIO_Input
PB8.GPIOParameters=GPIO_Label
PB8.GPIO_Label=OFFSET_LEFT
PB8.Signal=GPIO_Input
PB9.GPIOParameters=GPIO_Label
PB9.GPIO_Label=OFFSET_DOWN
PB9.Signal=GPIO_Input
PC0.GPIOParameters=GPIO_Label
PC0.GPIO_Label=OFFSET_COM
PC0.Signal=GPIO_Output
PC1.GPIOParameters=GPIO_Label
PC1.GPIO_Label=SCALE_B
PC1.Signal=GPIO_Input
PC10.GPIOParameters=GPIO_Label
PC10.GPIO_Label=UI_SCK
PC10.Mode=TX_Only_Simplex_Unidirect_Master
PC10.Signal=SPI3_SCK
PC11.GPIOParameters=GPIO_Label
PC11.GPIO_Label=UI_RCLK
PC11.Signal=GPIO_Output
PC12.GPIOParameters=GPIO_Label
PC12.GPIO_Label=UI_MOSI
PC12.Mode=TX_Only_Simplex_Unidirect_Master
PC12.Signal=SPI3_MOSI
PC13.GPIOParameters=GPIO_Label
PC13.GPIO_Label=OFFSET_CENTER
PC13.Signal=GPIO_Input
PC14-OSC32_IN.GPIOParameters=GPIO_Label
PC14-OSC32_IN.GPIO_Label=OFFSET_RIGHT
PC14-OSC32_IN.Signal=GPIO_Input
PC15-OSC32_OUT.GPIOParameters=GPIO_Label
PC15-OSC32_OUT.GPIO_Label=OFFSET_UP
PC15-OSC32_OUT.Signal=GPIO_Input
PC2.GPIOParameters=GPIO_Label
PC2.GPIO_Label=SCALE_A
PC2.Signal=GPIO_Input
PC3.GPIOParameters=GPIO_Label
PC3.GPIO_Label=SCALE_PUSH
PC3.Signal=GPIO_Input
PC4.GPIOParameters=GPIO_Label
PC4.GPIO_Label=TP906
PC4.Signal=GPIO_Output
PC5.GPIOParameters=GPIO_Label
PC5.GPIO_Label=TP907
PC5.Signal=GPIO_Output
PC6.GPIOParameters=GPIO_Label
PC6.GPIO_Label=MUX_A
PC6.Signal=GPIO_Output
PC7.GPIOParameters=GPIO_Label
PC7.GPIO_Label=MUX_B
PC7.Signal=GPIO_Output
PC8.GPIOParameters=GPIO_Label
PC8.GPIO_Label=MUX_C
PC8.Signal=GPIO_Output
PC9.GPIOParameters=GPIO_Label
PC9.GPIO_Label=MUX_INHIBIT
PC9.Signal=GPIO_Output
PF0-OSC_IN.Mode=HSE-External-Clock-Source
PF0-OSC_IN.Signal=RCC_OSC_IN
PF1-OSC_OUT.GPIOParameters=GPIO_Label
PF1-OSC_OUT.GPIO_Label=INPUT_COM
PF1-OSC_OUT.Signal=GPIO_Output
PF4.GPIOParameters=GPIO_Label
PF4.GPIO_Label=RX1_ADC
PF4.Mode=IN5-Single-Ended
PF4.Signal=ADC1_IN5
RCC.HSEPLLFreq_Value=8000000
RCC.HSE_VALUE=16000000
RCC.SYSCLKFreq_VALUE=72000000
RCC.SYSCLKSourceVirtual=RCC_SYSCLKSOURCE_PLLCLK
board=custom
